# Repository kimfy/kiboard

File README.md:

# kiboard
A repository for my custom keyboard. Inspired by /r/olkb, Ben Vallack, Ferris Sweep.

The name is a play on my initials (Kim I.)...

I initially started creating this keyboard with the ergogen tool but I converted over to KICAD. 

## Revision 3

Working on as of September 9th 2024.

Features I want to add:
- [ ] Third key on the thumb cluster.
- [ ] Artwork on the front and back (don't know what yet).

## List of products

[2x nice!nano v2](https://splitkb.com/products/nice-nano?variant=39408154116173)

[34x Kailh Hotswap Sockets](https://www.aliexpress.com/item/33023283633.html)

[34x Kailh Low Profile Switches (Brown)](https://www.aliexpress.com/item/32959996455.html)

[4x Blank MBK Choc Low Profile Keycaps](https://splitkb.com/products/blank-mbk-choc-low-profile-keycaps?variant=31811487039565)

[2x Mill Max Low Profile Sockets](https://splitkb.com/products/mill-max-low-profile-sockets?variant=31945995845709)

[2x JST Battery Connector (2p curved)](https://www.aliexpress.com/item/1005002096347570.html)

[2x Reset Button (b3u-1000p)](https://www.aliexpress.com/item/1005002267741606.html)

[2x Power Switch (pcm12)](https://www.aliexpress.com/item/4000685483225.html?)

[2x 3.7V Rechargable LiPo Battery (90mAh)](https://www.ebay.co.uk/itm/195234783901)

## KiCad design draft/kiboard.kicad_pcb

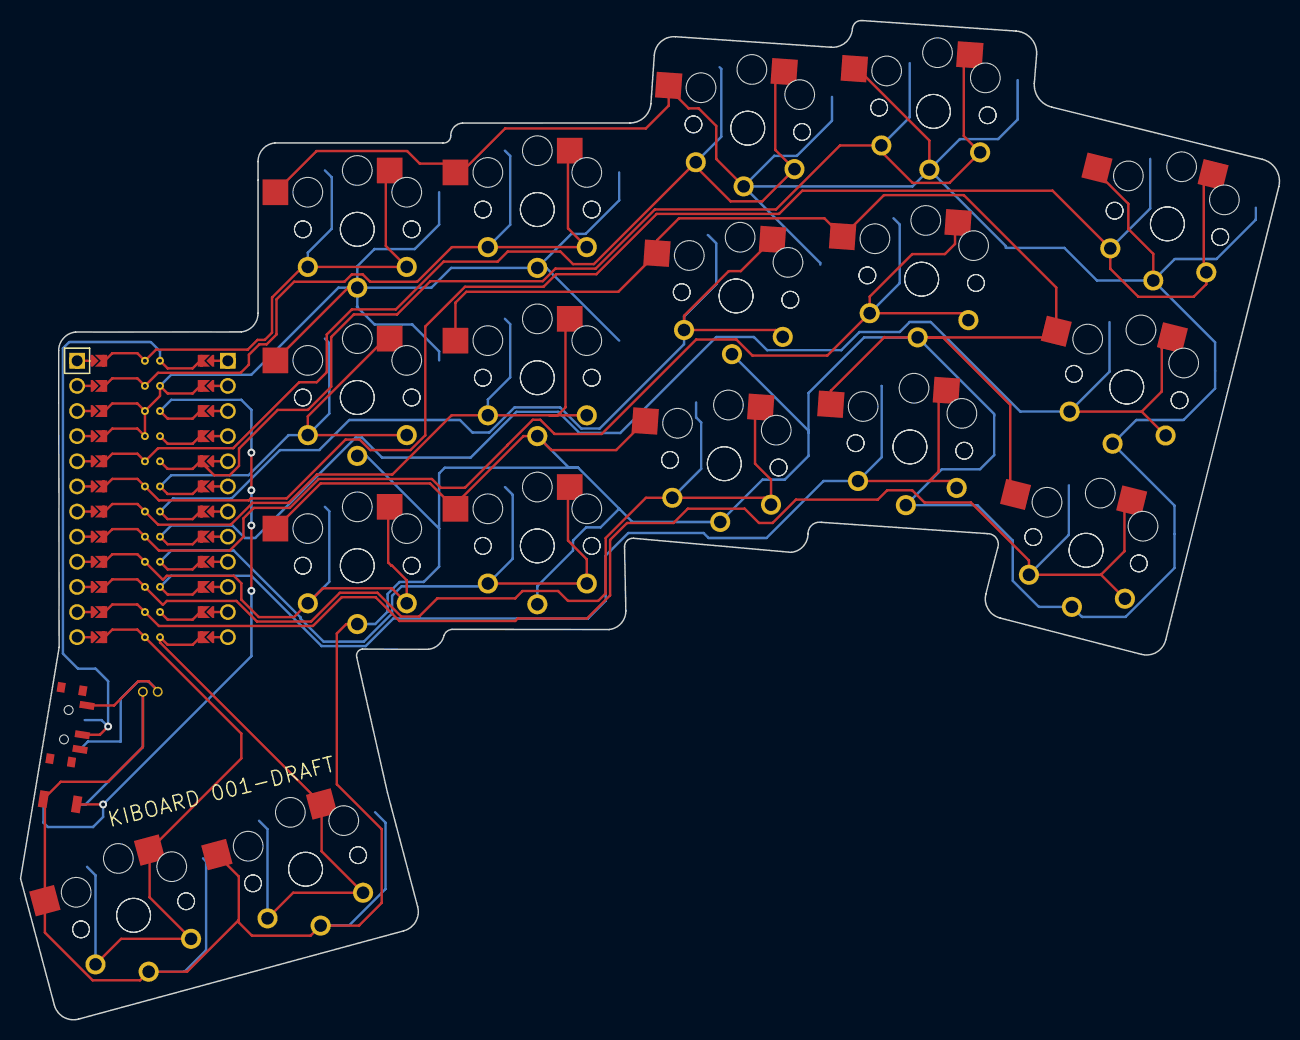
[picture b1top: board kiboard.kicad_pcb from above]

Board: 2 copper layers, 127.3 x 101.0 mm, 35 parts (0 on the bottom side), 18 nets.

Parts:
MCU1: ProMicro
S1, S2, S3, S4, S5, S6, S7, S8, S9, S10, S11, S12, S13, S14, S15, S16, S17, S18, S19, S20, S21, S22, S23, S24, S25, S26, S27, S28, S29, S30, S31, S32, S33, S34: PG1350

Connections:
GND: MCU1.2, MCU1.21, MCU1.22, S1.2, S2.2, S3.2, S4.2, S5.2, S6.2, S7.2, S8.2, S9.2, S10.2, S11.2, S12.2, S13.2, S14.2, S15.2, S16.2, S17.2, S18.2, S19.2, S20.2, S21.2, S22.2, S23.2, S24.2, S25.2, S26.2, S27.2, S28.2, S29.2, S30.2, S31.2, S32.2, S33.2, S34.2
Switch01: MCU1.24, S5.1, S6.1
Switch02: MCU1.23, S11.1, S12.1
Switch03: MCU1.20, S17.1, S18.1
Switch04: MCU1.5, S23.1, S24.1
Switch05: MCU1.19, S29.1, S30.1
Switch06: MCU1.6, S3.1, S4.1
Switch07: MCU1.18, S9.1, S10.1
Switch08: MCU1.7, S15.1, S16.1
Switch09: MCU1.17, S21.1, S22.1
Switch10: MCU1.8, S27.1, S28.1
Switch11: MCU1.16, S1.1, S2.1
Switch12: MCU1.9, S7.1, S8.1
Switch13: MCU1.15, S13.1, S14.1
Switch14: MCU1.10, S19.1, S20.1
Switch15: MCU1.14, S25.1, S26.1
Switch16: MCU1.13, S31.1, S32.1
Switch17: MCU1.12, S33.1, S34.1

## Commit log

2022-07-25 Initial upload
2022-07-26 Routing and edge cuts
2022-07-26 Added footprints from Ben Vallack's designs and modified routing a bit
2022-07-26 Finished routing
2022-07-26 Added products to README
2022-07-26 Added more products to README and finished up the first draft
2022-07-26 Gerbers, plot files and idk what changed on the board
2022-07-26 Order in README
2022-07-29 Gerbers and drill holes
2022-09-04 Revision 2: Move JST connector down a couple of millimeters. Connected ground properly
2024-09-09 feat!: rev3 WIP
